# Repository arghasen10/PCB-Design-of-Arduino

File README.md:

# PCB-Design-of-Arduino
Schematic and Layout of Arduino Uno Board.
One Ir receiver(Photodiode) is connected to pin A5.
One Push button is connected to pin D9

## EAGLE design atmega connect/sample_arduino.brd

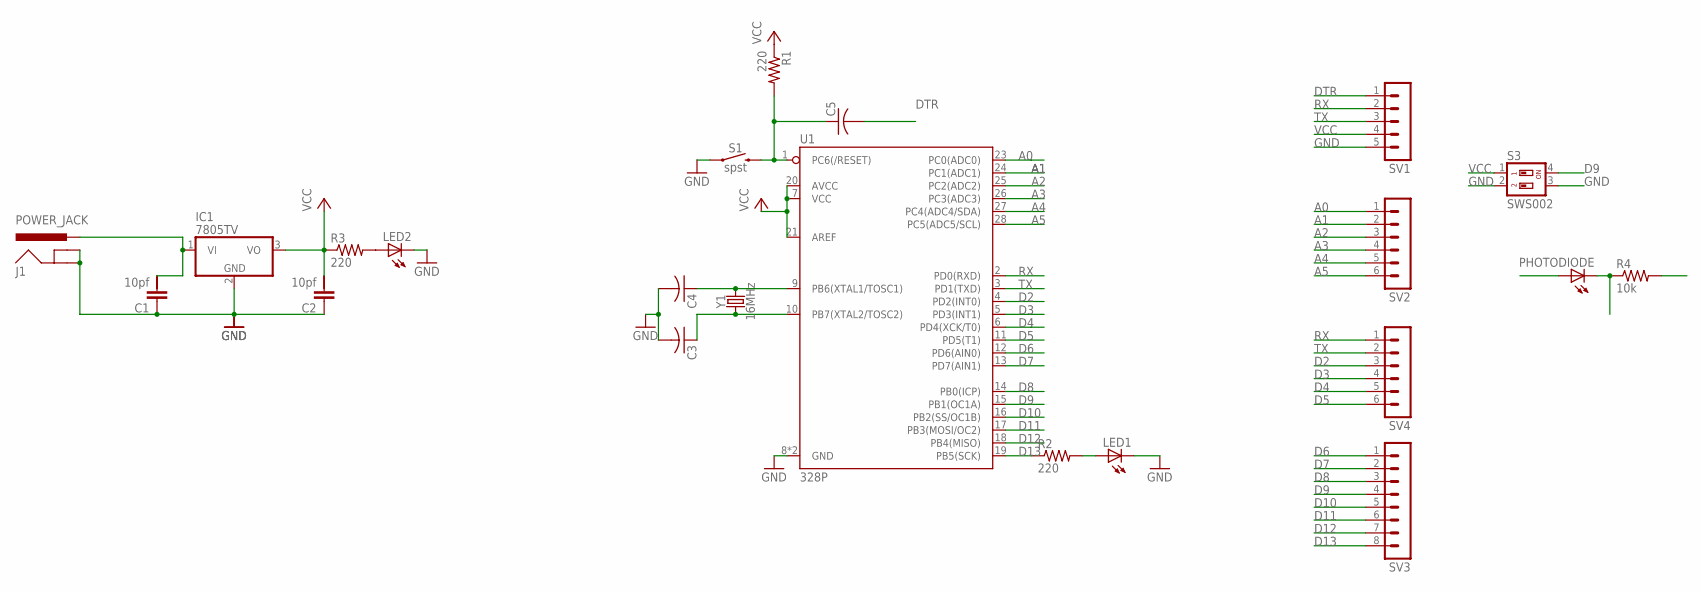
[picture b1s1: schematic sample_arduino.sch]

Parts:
C1, C2: 10pf; C2.5/5-6
C3, C4, C5: C-US025-024X044; C025-024X044
IC1: 7805TV; TO220V
J1: POWER_JACK; POWER_JACK_PTH
LED1, LED2: LED_ELD260; LED_LD260
PHOTODIODE: LED_ELD260; LED_LD260
R1, R2, R3: 220; 0204/7
R4: 10k; 0204/7
S1: spst; TACTILE_SWITCH_PTH_6.0MM
S3: SWS002; SMS-002
SV1: MA05-1
SV2, SV4: MA06-1
SV3: MA08-1
U1: 328P; DIP28
Y1: 16MHz; HC49US

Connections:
A0: SV2.1, U1.23 (PC0(ADC0))
A1: SV2.2, U1.24 (PC1(ADC1))
A2: SV2.3, U1.25 (PC2(ADC2))
A3: SV2.4, U1.26 (PC3(ADC3))
A4: SV2.5, U1.27 (PC4(ADC4/SDA))
A5: PHOTODIODE.K (C), R4.1, SV2.6, U1.28 (PC5(ADC5/SCL))
D2: SV4.3, U1.4 (PD2(INT0))
D3: SV4.4, U1.5 (PD3(INT1))
D4: SV4.5, U1.6 (PD4(XCK/T0))
D5: SV4.6, U1.11 (PD5(T1))
D6: SV3.1, U1.12 (PD6(AIN0))
D7: SV3.2, U1.13 (PD7(AIN1))
D8: SV3.3, U1.14 (PB0(ICP))
D9: S3.4, SV3.4, U1.15 (PB1(OC1A))
D10: SV3.5, U1.16 (PB2(SS/OC1B))
D11: SV3.6, U1.17 (PB3(MOSI/OC2))
D12: SV3.7, U1.18 (PB4(MISO))
D13: R2.1, SV3.8, U1.19 (PB5(SCK))
DTR: C5.2, SV1.1
GND: C1.1, C2.1, C3.2, C4.2, IC1.2 (GND), J1.GND, J1.GNDBREAK, LED1.K (C), LED2.K (C), PHOTODIODE.A, S1.1, S3.2, S3.3, SV1.5, U1.8 (GND), U1.22 (GND)
unnamed: C1.2, IC1.1 (VI), J1.PWR
unnamed: C4.1, U1.9 (PB6(XTAL1/TOSC1)), Y1.2
unnamed: C3.1, U1.10 (PB7(XTAL2/TOSC2)), Y1.1
unnamed: C5.1, R1.2, S1.3 (2), U1.1 (PC6(/RESET))
unnamed: LED2.A, R3.2
unnamed: LED1.A, R2.2
RX: SV1.2, SV4.1, U1.2 (PD0(RXD))
TX: SV1.3, SV4.2, U1.3 (PD1(TXD))
VCC: C2.2, IC1.3 (VO), R1.1, R3.1, R4.2, S3.1, SV1.4, U1.7 (VCC), U1.20 (AVCC), U1.21 (AREF)

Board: 2 copper layers, 22 parts (0 on the bottom side), 29 nets, no tracks yet.

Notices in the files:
parts and their libraries:
SparkFun-Connectors: Licensing: Creative Commons ShareAlike 4.0 International - https://creativecommons.org/licenses/by-sa/4.0
